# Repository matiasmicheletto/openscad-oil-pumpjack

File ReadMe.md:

# Parametric 3D model of an oil pumpjack

This is a Code-CAD based project that consists on the parametric modeling of all the parts of a scale oil pumpjack to be 3D-printed and driven by a 5V stepper motor. 

## Parameters of the model

This design is not based on any real model. Some basic parameters were selected to define the mechanical system dimensions.

An Octave simulation was used to test the resulting behavior of the machine depending on the selected parameters. The script was intended to optimize the design in some way and can be extended to perform a structural or a performance analysis.  

## Electronics 

To control the stepper motor position and speed, it is provided the design of a four-step sequencer that uses a two-bit counter based on JK master-slave flip-flops (74HC109) and an AND-gate based decoder (74HC08). A ULN2003 based driver (not displayed in the schematics) was used to amplify the output current of the sequencer.  

This circuit was implemented on a perfboard. A CAD PCB design is also provided which follows the perfboard layout, however, its recommended to modify it to build a better design in order to achieve a more aesthetic result.

## Printed model

The ready to print files are available in the [./stl](stl) folder.

### Additional materials

  - 13 bolts M2.5 x 25mm  
  - 17 nuts M2.5  
  - 1 bolt M5 x 65 mm  
  - 5 nuts M5  
  - 4 thumbtacks  
  - 1 150x90x20 mm wood plank

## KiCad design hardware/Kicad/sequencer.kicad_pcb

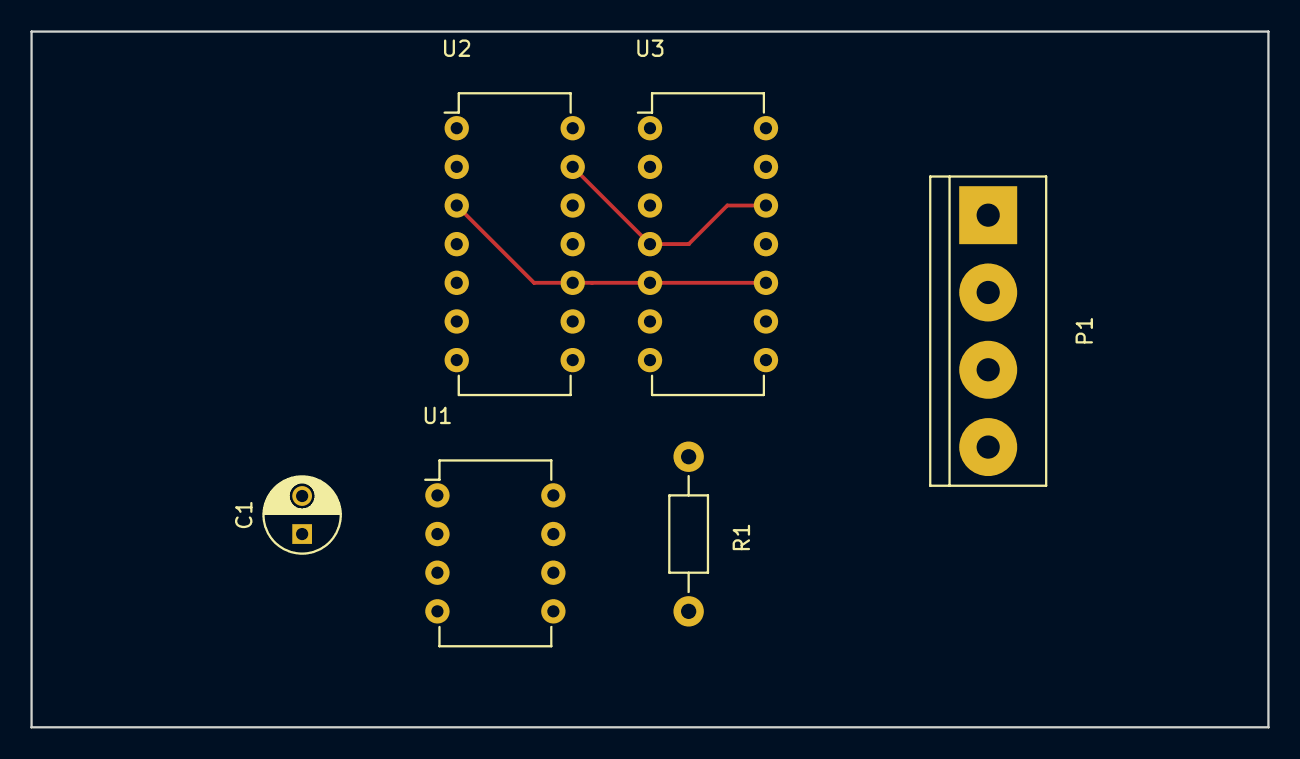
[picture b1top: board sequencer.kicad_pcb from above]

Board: 2 copper layers, 81.3 x 45.7 mm, 6 parts (0 on the bottom side), 13 nets.

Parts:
C1: CP_Small; C_Radial_D5_L11_P2.5
P1: CONN_01X04; bornier4
R1: R_Small; Resistor_Horizontal_RM10mm
U1: LM555N; DIP-8_W7.62mm
U2: 74LS109; DIP-14_W7.62mm
U3: 74LS08; DIP-14_W7.62mm

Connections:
GND: C1.2, U1.1, U2.8, U3.7
unnamed: C1.1, U1.2, U1.6
unnamed: P1.1, U3.3
unnamed: P1.2, U3.6
unnamed: P1.3, U3.8
unnamed: P1.4, U3.11
unnamed: R1.2, U1.7
unnamed: U1.3, U2.4, U2.12
unnamed: U2.6, U3.1
unnamed: U2.9, U3.2, U3.13
unnamed: U2.2, U2.3, U2.10, U3.5, U3.10
unnamed: U2.7, U2.13, U2.14, U3.4, U3.9, U3.12
VCC: R1.1, U1.4, U1.8, U2.1, U2.5, U2.11, U3.14

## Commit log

2019-12-03 Primer commit
2019-12-03 Piezas soporte mecanismo accionamiento
2019-12-03 Disegno electronico Kicad (sin terminar) y Proteus (para plaq. univ.)
2019-12-04 Primera impresion 3D
2019-12-09 Modelo scad cabezal. Renombre archivos. Imagenes modelo
2019-12-11 Desplazamiento del acople cabezal. Simulaciones octave para calibrar medidas
2019-12-11 Optimizacion de la simulacion
2019-12-12 Modelos como modulos independientes
2019-12-13 Dimensiones definidas. TODO: aplicar a todas las piezas
2019-12-13 Nuevas medidas. TODO: Soporte del balancin
2019-12-15 Ajuste dimensiones. Pie soporte balancin. Presentacion partes
2019-12-15 Reorganizacion figuras. Edicion ReadMe
2019-12-15 Disposicion de piezas para impresion
2019-12-15 STL de cada pieza
2019-12-19 Ajuste diametro eje bielas. Gif animado con Python.
2019-12-19 Fix medidas cabeza de mula y ecualizador
2019-12-20 Arandelas de relleno para ecualizador y manivelas
2019-12-20 Lista de materiales
2019-12-21 Reemplazo de las poleas por engranajes
2019-12-23 Actualizacion stl de todas las piezas
2020-01-16 Galeria. Actualizacion ReadMe.
2020-01-16 Actualizacion ReadMe
2021-08-22 Traduccion Readme, script y algunos modulos
2021-08-29 Translated comments
2021-08-31 Crank and Equalizer implementations in JScad
2021-09-03 Block, Fillers and Pitmans arms implementations in JScad
2021-09-06 Jscad implementation of all parts. GUI for parameter configuration
2021-09-06 JScad model: print layout switcher
2021-09-09 JScad model: parametrized positions
2021-09-09 JScad model: model physics
2021-09-09 Openscad animated model
2021-09-09 Printing layout update
2021-09-10 Readme update
2021-10-10 Mark II (3rd class lever pumpjack)
2021-10-11 Mark II and horse head geometry fixes
2021-10-11 Couloured parts
